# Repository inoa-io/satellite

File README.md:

# Inoa Satellite

The Inoa Satellite is a lightweight and secure gateway for your fuse box or industrial environment.

Please see our [Project Pages](https://inoa-io.github.io/satellite/) for details.

## Why?

There is a huge amount of IoT gateways out there, but none of these fulfill completely all of our design goals:

* Usage in a rough industrial environment
* Hardware driven security (HSM)
* Inexpensive hardware to be able to finance a huge fleet of devices
* Low energy consumption
* Fuse box casing (DIN rail)
* Small (2 FE / 36 mm) to allow mounting in existing fuse boxes
* Extendable design to be future proof
* Modular design to adapt hardware to use cases and keep costs low

## How?

We use [KiCad](https://www.kicad.org/) for our PCB designs, [Parts Community](https://b2b.partcommunity.com/) and [SnapEDA](https://www.snapeda.com/) for symbols, footprints, models 'n stuff...

To meet our design goals, we decided to:

* Use the ESP32
* Use the ATECC family of chips as HSM
* Choose industrial proof parts, shielding and ESD protection
* Pick a certified DIN rail casing
* Cut the design to several stacked modules

## Modules

### General

The Satellite comes with a stacked design allowing to interchange the modules on each level of the stack to fit the needs of its planned duty.

This allows quick and cheap adjustment of single devices, ensures expandability, keeps costs low and offers replacement of defect modules with spare parts.

The Satellite consists of up to 4 levels (level 1 is the bottom). Level 3 is an optional level and may be left out.

* Level 1 holds the power supply and metering / control peripheries.
* Level 2 is the main module for the micro controller
* Level 3 is the network / communication level (Ethernet, NB IoT, LoRa, ...)
* Level 4 is meant for the user panel

### Metering Modules

#### Electric Metering Module

The electric metering module is dedicated to be used for interacting with electric meters, inverters, batteries and so on. It is a base module on level 1 of the stack. Its features are:

* 5V-24V power input
* PE / Shield pin
* 2x RS485 interface (used for e.g. ModBus, ...)
* 2x pulse interface (S0, Photoelectric barrier, ...)
* 2x relay driver

#### CT Metering Module

The CT module is dedicated to be used for EMS use cases. Current transformers (split core) with voltage output may be used (e.g. SCT-013).

It is a base module on level 1 of the stack. Its features are:

* 5V-24V power input
* 3x CT
* 1x Analog in (ADC)
* 1x Digital in (e.g. S0 meters)
* 1x RS485 interface (ModBus RTU meters)

#### MBus / WMBus Metering Module

The M-Bus module is dedicated to be used for interacting with different meters via RS485 or M-Bus. The module acts as M-Bus master, but a separate power supply is needed. Because the size of this power supply depends on the amount of connected meters, we decided to give the ability to choose a fitting, external power supply.

The M-Bus module is a base module on level 1 of the stack. Its features are:

* 5V-24V power input
* 1x M-Bus interface
* 1x RS485 interface (ModBus RTU meters)
* 2x pulse interface (S0 meters)
* PE / Shield pins for bus connections

### SoC Module

The SoC module is the heart of the satellite and home of the microprocessor, flash memory and HSM (hardware security module). It is the main module on level 2 of the stack. Its features are:

* ESP32 MPU (32 Bit, Dual Core, 240 MHz)
* 8 MB RAM
* 16 MB flash
* µSD Card slot for external storage
* HSM (ATECC608)

### Ethernet Module

The Ethernet module connects the Satellite to Ethernet. It is a network module on level 3 of the stack. Its features are:

* W5500 Ethernet chip (MAC+PHY)
* ESD protection
* Shielded RJ45 plug

### NB IoT Module

_**Coming soon**_

### LoRa Module

_**Coming soon**_

### Panel Module

The panel module is the "user interface" and home of all user input output devices of the Satellite. It is the top module on level 4. Its features are:

* Power and status LED
* Reset and setup button
* 128x64 OLED display (optional)
* RS232 Debug interface
* External WiFi antenna (optional)

## Casings

We use a DIN rail mounted casing in 2 FE width. See [Datasheet](./casing/rail/apra_rail_Leiterkartengroessen_PCB_Dimensions_de_en.pdf) for details.

## Development

### Building the Project

You will need:

* Python >= 3.8
* [KiBot](https://github.com/INTI-CMNB/KiBot) (see [installation instructions](https://github.com/INTI-CMNB/KiBot#installation-on-ubuntu-or-debian))

Clone this project and run `./build.sh`. You will get a selection of the possible modules to be built. Tests will be executed and the build result is placed in the `out` folder.

### Project structure

| Folder               | Purpose |
|----------------------|---------|
| ./casing             | Construction files for the casing          |
| ./configs            | KiCad-Export configuration                 |
| ./development-board  | Design for the development board           |
| ./docs               | Documentation                              |
| ./ethernet-extension | Design for the Ethernet module             |
| ./libraries          | Electric symbols, footprints and 3D models |
| ./metering-module    | Design for the metering module             |
| ./nbiot-extension    | Design for the NB IoT module               |
| ./out                | Build output folder                        |
| ./panel-module       | Design for the panel module                |
| ./soc-module         | Design for the SoC module                  |

### Conventions

#### Markings

* Each PCB has an etched label for "TOP" and "BOT" marks
* Each PCB has an etched label for the product serial following the pattern: SR-XX-NNN (e.g. SR-SM-021)
* The product serial start with "SR" for "Satellite Rail", the next two characters are reserved for the module, the 3 digits represents the version

| Serial    | Module / Part          | Current Version |
|-----------|------------------------|-----------------|
| SR-SC-XXX | SoC Module             | v2.0            |
| SR-EM-XXX | Electric Metering      | v2.0            |
| SR-CM-XXX | Current Loop Metering  | v2.0            |
| SR-MM-XXX | MBus / WMBus Metering  | v2.0            |
| SR-ET-XXX | Ethernet Module        | v2.0            |
| SR-NB-XXX | NB IoT Module          | v2.0            |
| SR-LR-XXX | LoRa / LoRa WAN Module | v2.0            |
| SR-PN-XXX | Panel Module           | v2.0            |

#### Tracks / Vias / Grids

Despite of the low energy consumption of the MCU itself, we are planning with a maximum current of 1A to be future proof for extra extensions that have a higher energy demand (LoRa, NB IoT, ...).

We chose two different of track widths for main power and for data lines (0.25 mm / 0.5 mm) and planned a minimum temperature of 0°C. See the table below.

| Track (mm) | Track (mil) | 10°  | 20°  | 30°  | 40°  | 50°  | 60°  |
|------------|-------------|------|------|------|------|------|------|
| 0.1mm      | 4mil        | 0.4A | 0.6A | 0.8A | 0.9A | 1.0A | 1.1A |
| 0.2mm      | 8mil        | 0.7A | 1.0A | 1.2A | 1.4A | 1.6A | 1.7A |
| 0.3mm      | 12mil       | 0.9A | 1.3A | 1.6A | 1.8A | 2.0A | 2.2A |
| 0.4mm      | 16mil       | 1.1A | 1.5A | 1.9A | 2.2A | 2.4A | 2.7A |
| 0.5mm      | 20mil       | 1.3A | 1.8A | 2.2A | 2.5A | 2.8A | 3.1A |
| 0.6mm      | 24mil       | 1.4A | 2.0A | 2.4A | 2.8A | 3.1A | 3.4A |

We chose a 0.1mm grid for all PCB designs, because our casings and mechanics are also measured in millimeters.

We chose 0.8mm 0.4mm vias.

## Pin Out

| Pin ESP | Pin Satellite | Pin Name  | Standard Purpose     |
|---------|---------------|-----------|----------------------|
| 1       | East 1        | GND       | Ground               |
| 2       | West 1        | 3V3       | Power supply         |
| 3       | West 2        | EN3       | Reset                |
| 4       | West 3        | I36       | I2C Interrupt        |
| 5       | West 4        | I39       | UART 1 RX            |
| 6       | West 5        | I34       | SPI 2 MISO           |
| 7       | West 6        | I35       | UART 2 RX            |
| 8       | West 7        | IO32      | SPI 2 MOSI           |
| 9       | West 8        | IO33      | SPI 2 CLK            |
| 10      | West 9        | IO25      | UART 1 TXE           |
| 11      | West 10       | IO26      | UART 1 TX            |
| 12      | West 11       | IO27      | SPI 2 CS (Ethernet)  |
| 13      | West 12       | IO14      | Ethernet Reset       |
| 14      | West 13       | IO12      |                      |
| 15      | NC            | GND       | Ground               |
| 16      | West 14       | IO13      | Status LED           |
| 17      | NC            | NC        | Internal Flash / RAM |
| 18      | NC            | NC        | Internal Flash / RAM |
| 19      | NC            | NC        | Internal Flash / RAM |
| 20      | NC            | NC        | Internal Flash / RAM |
| 21      | NC            | NC        | Internal Flash / RAM |
| 22      | NC            | NC        | Internal Flash / RAM |
| 23      | East 13       | IO15      | UART 2 TX            |
| 24      | East 12       | IO2       | UART 2 TXE           |
| 25      | East 11       | IO0       | Setup Button         |
| 26      | East 10       | IO4       | Ethernet Interrupt   |
| 27      | NC            | NC        | Internal Flash / RAM |
| 28      | NC            | NC        | Internal Flash / RAM |
| 29      | East 9        | IO5       | SPI 1 CS (SD)        |
| 30      | East 8        | IO18      | SPI 1 CLK            |
| 31      | East 7        | IO19      | SPI 1 MISO           |
| 32      | NC            | NC        | Internal Flash / RAM |
| 33      | East 6        | IO21      | I2C SDA              |
| 34      | East 5        | URXD0     | UART 0 RX            |
| 35      | East 4        | UTXD0     | UART 0 TX            |
| 36      | East 3        | IO22      | I2C SCL              |
| 37      | East 2        | IO23      | SPI 1 MOSI           |
| 38      | East 1        | GND       | Ground               |
| NC      | East 14       | Shield    | Shield / PE          |

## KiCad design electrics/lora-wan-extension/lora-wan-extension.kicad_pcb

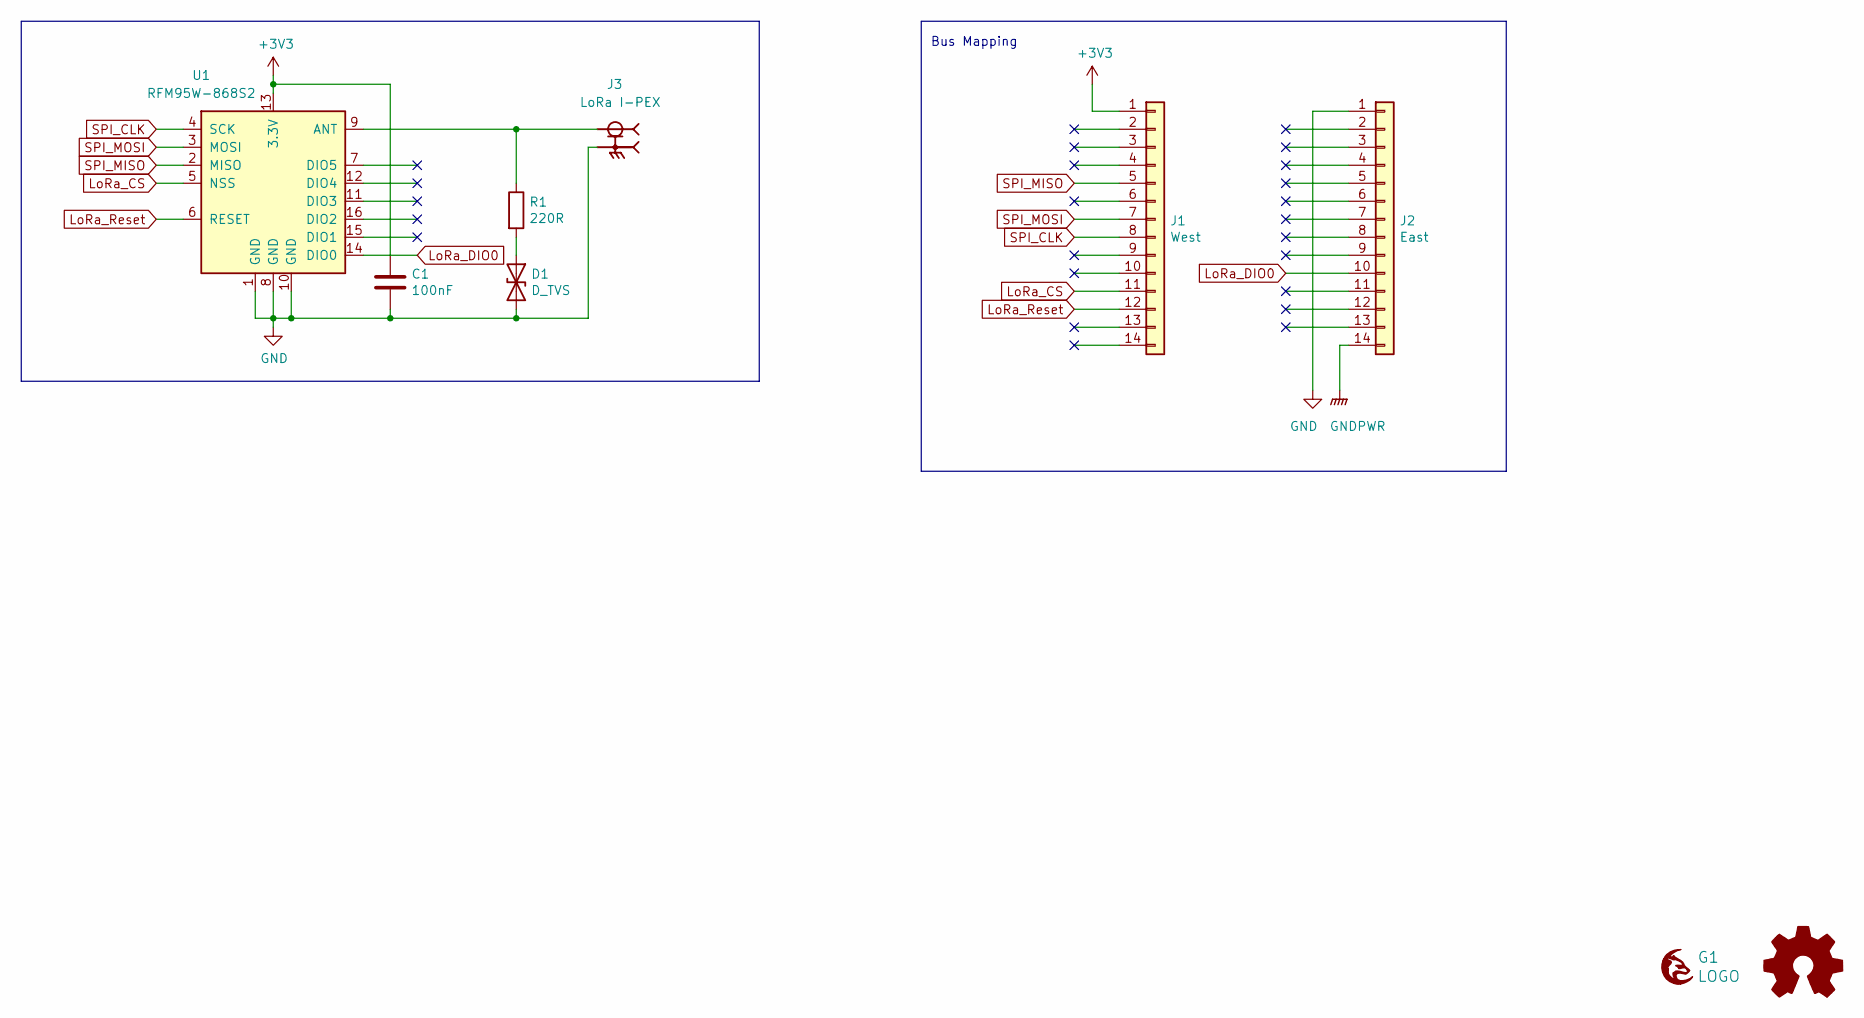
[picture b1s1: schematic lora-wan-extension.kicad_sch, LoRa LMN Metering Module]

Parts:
C1: 100nF; C_1206_3216Metric_Pad1.33x1.80mm_HandSolder; mouser# 80-C1206C104M6R
D1: D_TVS; D_0603_1608Metric_Pad1.05x0.95mm_HandSolder; mouser# 652-CG0603MLC-3.3LE
G1: LOGO; grayc-logo-negative
G2: Logo_Open_Hardware_Small; OSHW-Logo2_7.3x6mm_SilkScreen
J1: West; PinHeader_1x14_P2.54mm_Vertical; mouser# 437-8018701453001101
J2: East; PinHeader_1x14_P2.54mm_Vertical; mouser# 437-8018701453001101
J3: LoRa I-PEX; SAMTEC_RSP-122811-01; PARTREV H; mouser# 200-RSP-122811-01
R1: 220R; R_1206_3216Metric_Pad1.30x1.75mm_HandSolder; mouser# 71-RCG1206220RJNEA
U1: RFM95W-868S2; XCVR_RFM69HW-868S2; mouser# 223-RFM95W-868S2

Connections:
+3V3: C1.1, J1.1, U1.13 (3.3V)
GND: C1.2, D1.2 (A2), J2.1, J3.G1, J3.G2, U1.1 (GND), U1.8 (GND), U1.10 (GND)
GNDPWR: J2.14
LoRa_CS: J1.11, U1.5 (NSS)
LoRa_DIO0: J2.10, U1.14 (DIO0)
LoRa_Reset: J1.12, U1.6 (RESET)
unnamed: D1.1 (A1), R1.2
unnamed: J3.1, R1.1, U1.9 (ANT)
SPI_CLK: J1.8, U1.4 (SCK)
SPI_MISO: J1.5, U1.2 (MISO)
SPI_MOSI: J1.7, U1.3 (MOSI)

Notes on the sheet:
Bus Mapping

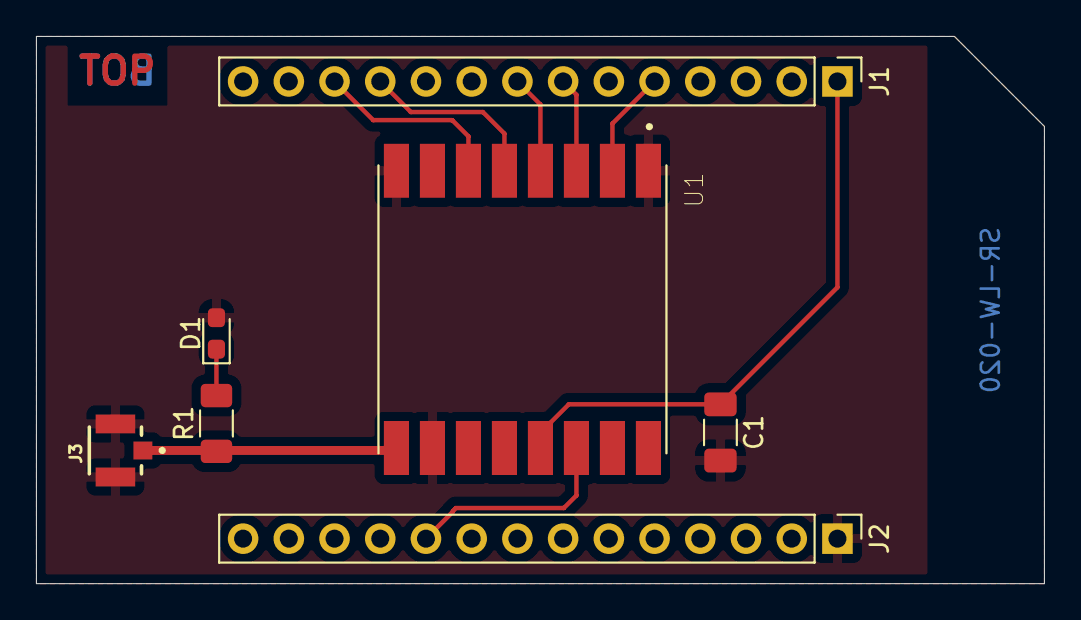
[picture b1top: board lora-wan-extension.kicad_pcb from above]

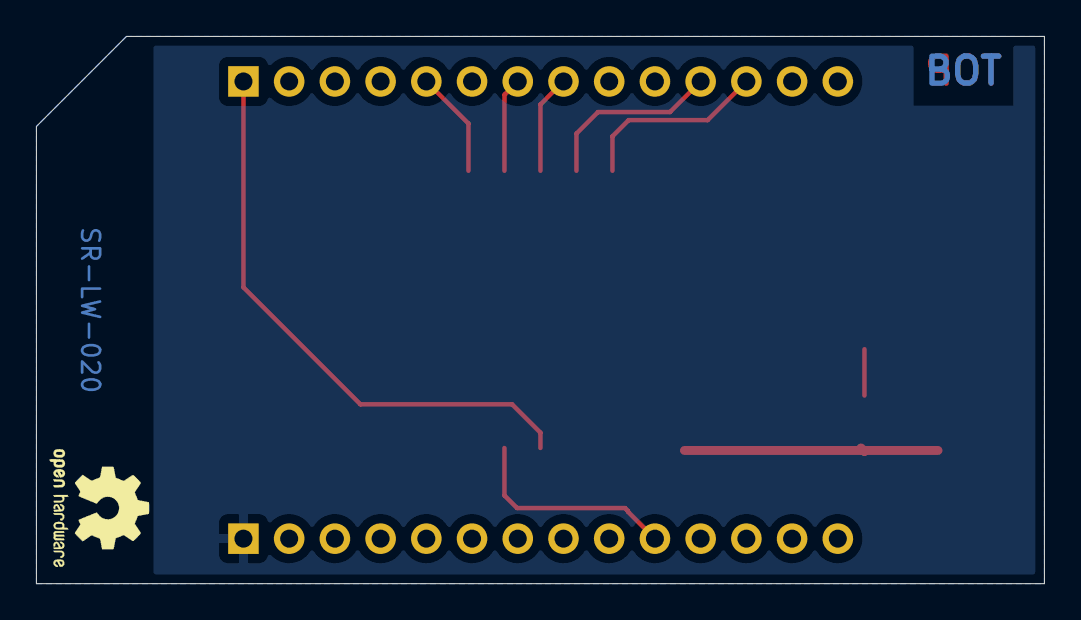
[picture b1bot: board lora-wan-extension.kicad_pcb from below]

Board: 2 copper layers, 56.0 x 30.4 mm, 9 parts (2 on the bottom side), 10 nets.

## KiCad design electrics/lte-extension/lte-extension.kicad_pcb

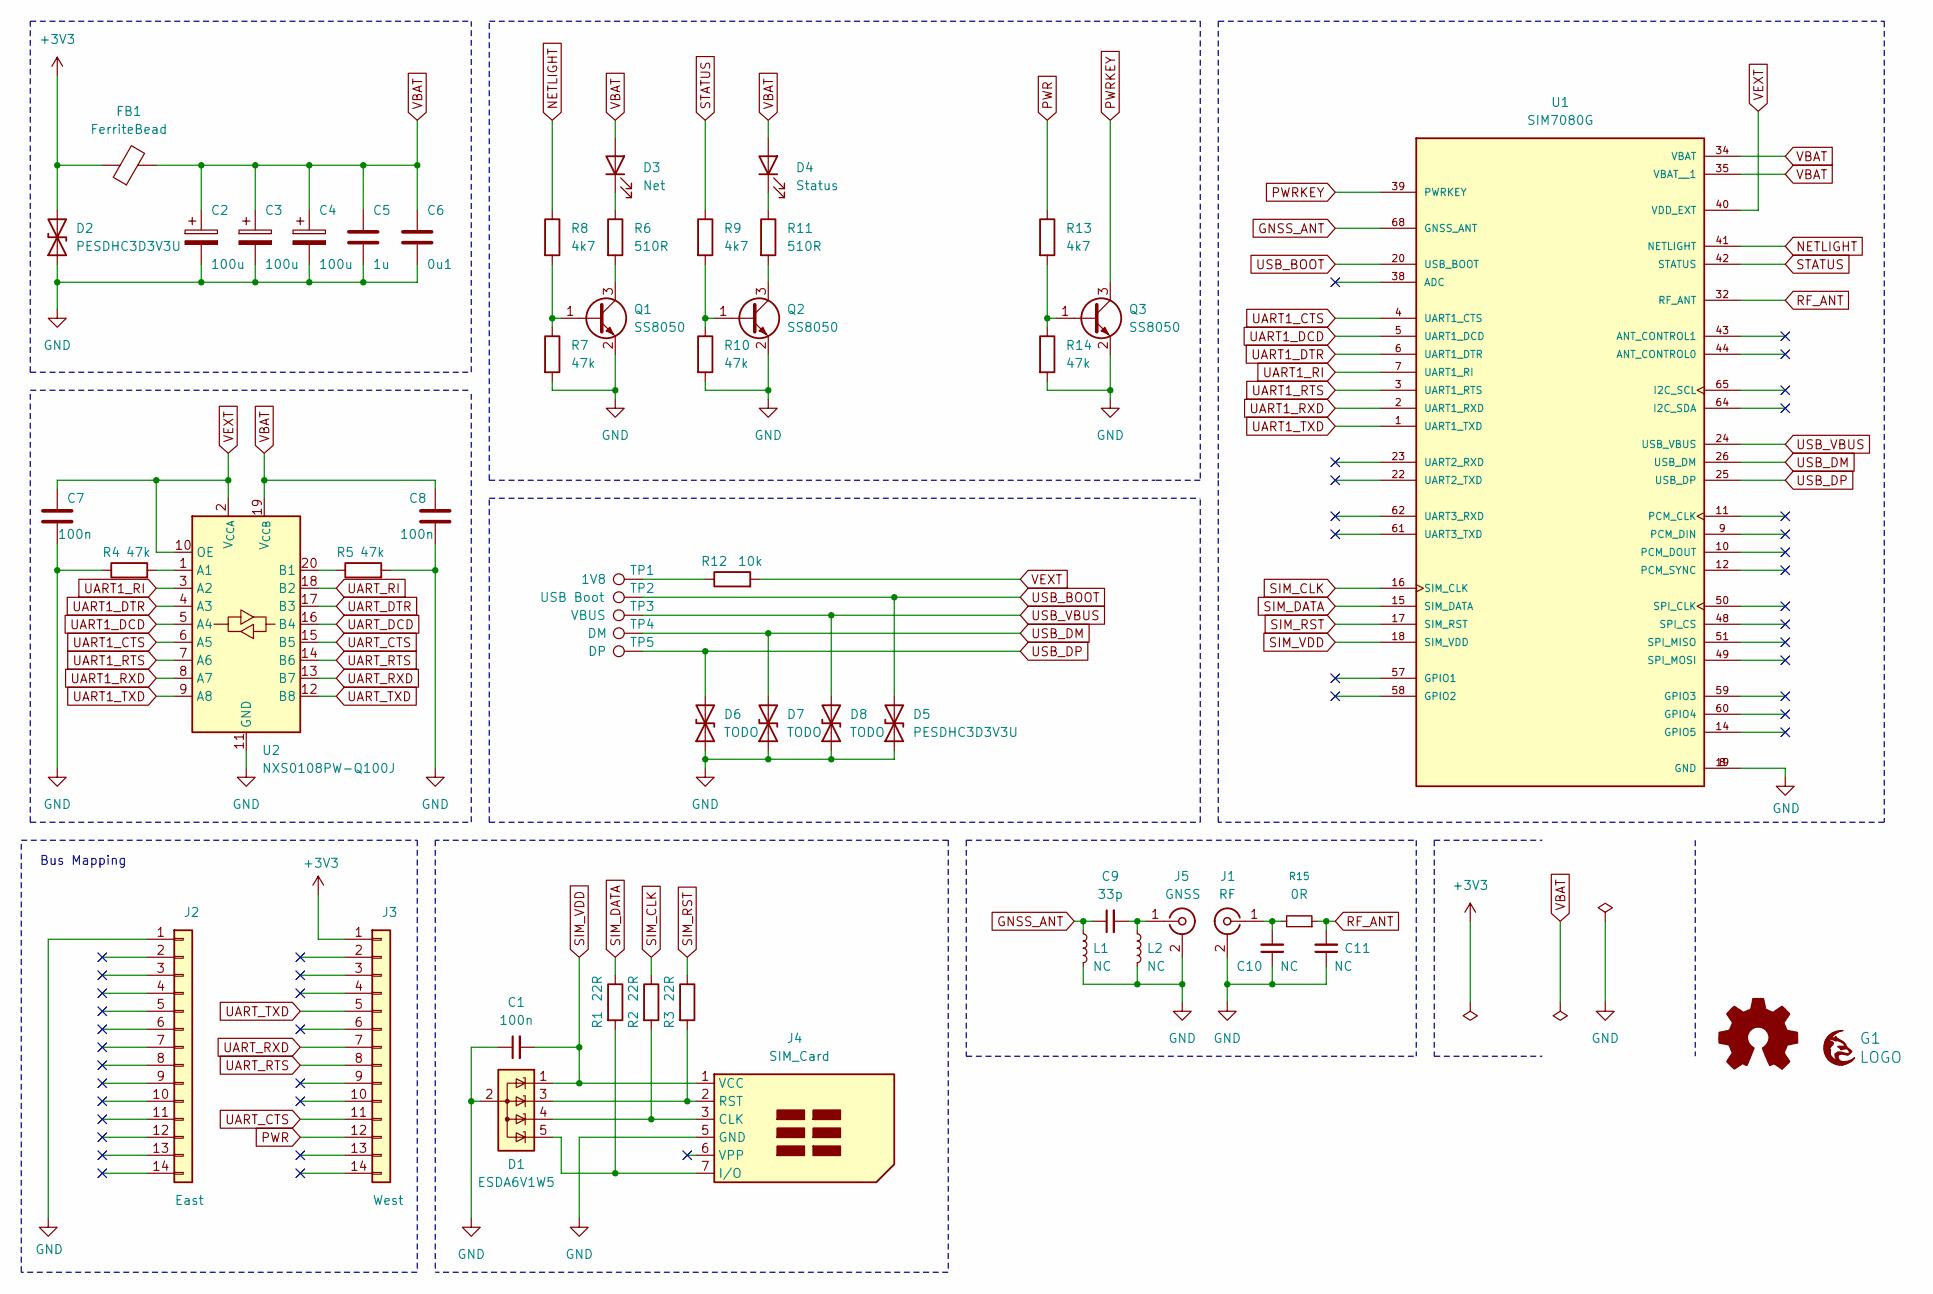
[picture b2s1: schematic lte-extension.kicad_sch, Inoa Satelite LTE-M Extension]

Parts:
C1, C7, C8: 100n; C_0603_1608Metric_Pad1.08x0.95mm_HandSolder
C2, C3, C4: 100u; CP_EIA-2012-12_Kemet-R_HandSolder
C5: 1u; C_0603_1608Metric_Pad1.08x0.95mm_HandSolder
C6: 0u1; C_0603_1608Metric_Pad1.08x0.95mm_HandSolder
C9: 33p; C_0603_1608Metric_Pad1.08x0.95mm_HandSolder
C10, C11: NC; C_0603_1608Metric_Pad1.08x0.95mm_HandSolder
D1: ESDA6V1W5; SOT65P210X110-5N
D2, D5: PESDHC3D3V3U; D_SOD-323F
D3: Net; LED_0603_1608Metric
D4: Status; LED_0603_1608Metric
D6, D7, D8: TODO; D_SOD-323F
FB1: FerriteBead; L_0805_2012Metric
G1: LOGO; grayc-logo-negative
G2: Logo_Open_Hardware_Small; OSHW-Logo2_7.3x6mm_SilkScreen
J1: RF; IPEX_20279-001E-01
J2: East; PinHeader_1x14_P2.54mm_Vertical; mouser# 437-8018701453001101
J3: West; PinHeader_1x14_P2.54mm_Vertical; mouser# 437-8018701453001101
J4: SIM_Card; nanoSIM_Hinged_CUI_NSIM-2-C
J5: GNSS; IPEX_20279-001E-01
L1, L2: NC; L_0603_1608Metric_Pad1.05x0.95mm_HandSolder
Q1, Q2, Q3: SS8050; SOT-23
R1, R2, R3: 22R; R_0603_1608Metric_Pad0.98x0.95mm_HandSolder
R4, R5, R7, R10, R14: 47k; R_0603_1608Metric_Pad0.98x0.95mm_HandSolder
R6, R11: 510R; R_0603_1608Metric_Pad0.98x0.95mm_HandSolder
R8, R9, R13: 4k7; R_0603_1608Metric_Pad0.98x0.95mm_HandSolder
R12: 10k; R_0603_1608Metric_Pad0.98x0.95mm_HandSolder
R15: 0R; R_0603_1608Metric_Pad0.98x0.95mm_HandSolder
TP1: 1V8; TestPoint_Pad_D1.0mm
TP2: USB Boot; TestPoint_Pad_D1.0mm
TP3: VBUS; TestPoint_Pad_D1.0mm
TP4: DM; TestPoint_Pad_D1.0mm
TP5: DP; TestPoint_Pad_D1.0mm
U1: SIM7080G; XCVR_SIM7080G; PARTREV 1.04
U2: NXS0108PW-Q100J; TSSOP-20_4.4x6.5mm_P0.65mm

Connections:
+1V8: C7.1, R12.2, U1.40 (VDD_EXT), U2.2 (V_{CCA}), U2.10 (OE)
+3V3: D2.2 (A2), FB1.1, J3.1
GND: C1.1, C2.2, C3.2, C4.2, C5.2, C6.2, C7.2, C8.2, C10.1, C11.1, D1.2 (A), D2.1 (A1), D5.1 (A1), D6.1 (A1), D7.1 (A1), D8.1 (A1), J1.2 (Ext), J2.1, J4.5 (GND), J5.2 (Ext), L1.2, L2.2, Q1.2 (E), Q2.2 (E), Q3.2 (E), R4.1, R5.2, R7.2, R10.2, R14.2, U1.8 (GND), U1.13 (GND), U1.19 (GND), U1.21 (GND), U1.27 (GND), U1.30 (GND), U1.31 (GND), U1.33 (GND), U1.36 (GND), U1.37 (GND), U1.45 (GND), U1.63 (GND), U1.66 (GND), U1.67 (GND), U1.69 (GND), U1.70 (GND), U1.71 (GND), U1.72 (GND), U1.73 (GND), U1.74 (GND), U1.75 (GND), U1.76 (GND), U1.77 (GND), U2.11 (GND), U2.21 (GND)
GNDPWR: J2.14
GNSS_ANT: C9.1, L1.1, U1.68 (GNSS_ANT)
NETLIGHT: R8.1, U1.41 (NETLIGHT)
unnamed: D3.1 (K), R6.1
unnamed: D4.1 (K), R11.1
unnamed: C10.2, J1.1 (In), R15.2
unnamed: D1.4 (K), J4.3 (CLK), R2.2
unnamed: D1.5 (K), J4.7 (I/O), R1.2
unnamed: D1.3 (K), J4.2 (RST), R3.2
unnamed: C9.2, J5.1 (In), L2.1
unnamed: Q1.1 (B), R7.1, R8.2
unnamed: Q1.3 (C), R6.2
unnamed: Q2.1 (B), R9.2, R10.1
unnamed: Q2.3 (C), R11.2
unnamed: Q3.1 (B), R13.2, R14.1
unnamed: R12.1, TP1.1
unnamed: R4.2, U2.1 (A1)
unnamed: R5.1, U2.20 (B1)
PWR: J3.12, R13.1
PWRKEY: Q3.3 (C), U1.39 (PWRKEY)
RF_ANT: C11.2, R15.1, U1.32 (RF_ANT)
SIM_CLK: R2.1, U1.16 (SIM_CLK)
SIM_DATA: R1.1, U1.15 (SIM_DATA)
SIM_RST: R3.1, U1.17 (SIM_RST)
SIM_VDD: C1.2, D1.1 (K), J4.1 (VCC), U1.18 (SIM_VDD)
STATUS: R9.1, U1.42 (STATUS)
UART1_CTS: U1.4 (UART1_CTS), U2.6 (A5)
UART1_DCD: U1.5 (UART1_DCD), U2.5 (A4)
UART1_DTR: U1.6 (UART1_DTR), U2.4 (A3)
UART1_RI: U1.7 (UART1_RI), U2.3 (A2)
UART1_RTS: U1.3 (UART1_RTS), U2.7 (A6)
UART1_RXD: U1.2 (UART1_RXD), U2.8 (A7)
UART1_TXD: U1.1 (UART1_TXD), U2.9 (A8)
UART_CTS: J3.11, U2.15 (B5)
UART_DCD: U2.16 (B4)
UART_DTR: U2.17 (B3)
UART_RI: U2.18 (B2)
UART_RTS: J3.8, U2.14 (B6)
UART_RXD: J3.7, U2.13 (B7)
UART_TXD: J3.5, U2.12 (B8)
USB_BOOT: D5.2 (A2), TP2.1, U1.20 (USB_BOOT)
USB_DM: D7.2 (A2), TP4.1, U1.26 (USB_DM)
USB_DP: D6.2 (A2), TP5.1, U1.25 (USB_DP)
USB_VBUS: D8.2 (A2), TP3.1, U1.24 (USB_VBUS)
VBAT: C2.1, C3.1, C4.1, C5.1, C6.1, C8.1, D3.2 (A), D4.2 (A), FB1.2, U1.34 (VBAT), U1.35 (VBAT__1), U2.19 (V_{CCB})

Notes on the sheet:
Bus Mapping

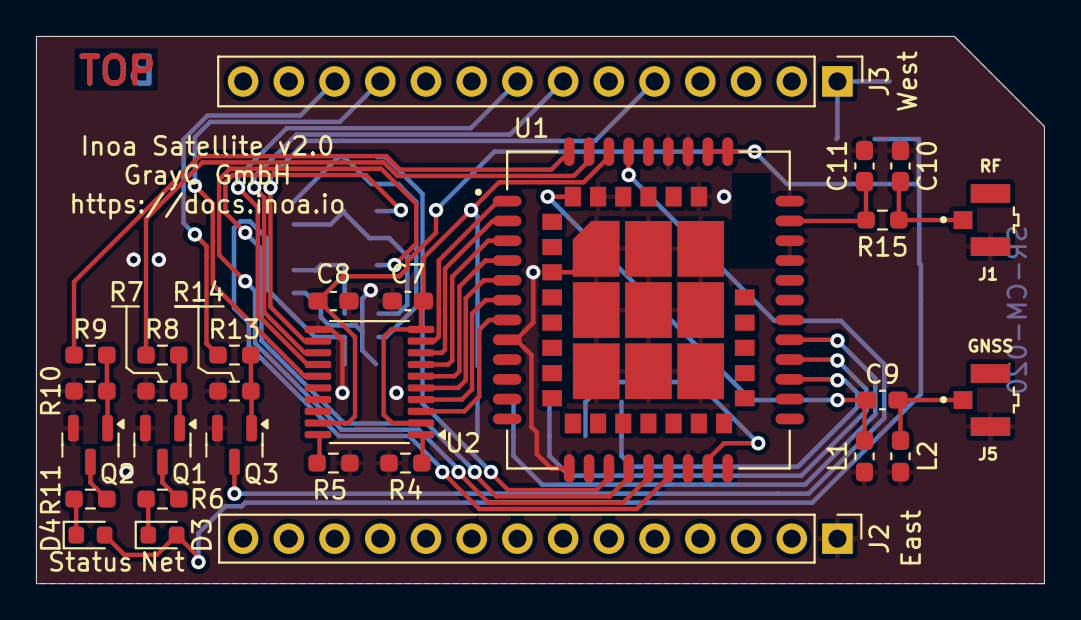
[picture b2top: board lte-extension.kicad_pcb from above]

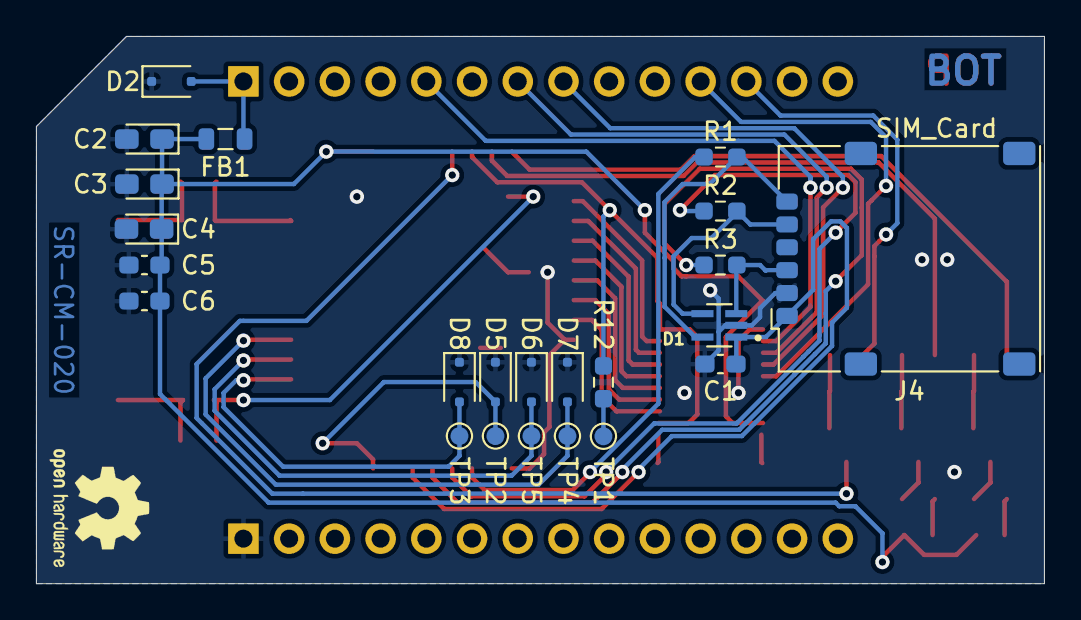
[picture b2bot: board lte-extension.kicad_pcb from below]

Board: 2 copper layers, 56.0 x 30.4 mm, 54 parts (25 on the bottom side), 44 nets.

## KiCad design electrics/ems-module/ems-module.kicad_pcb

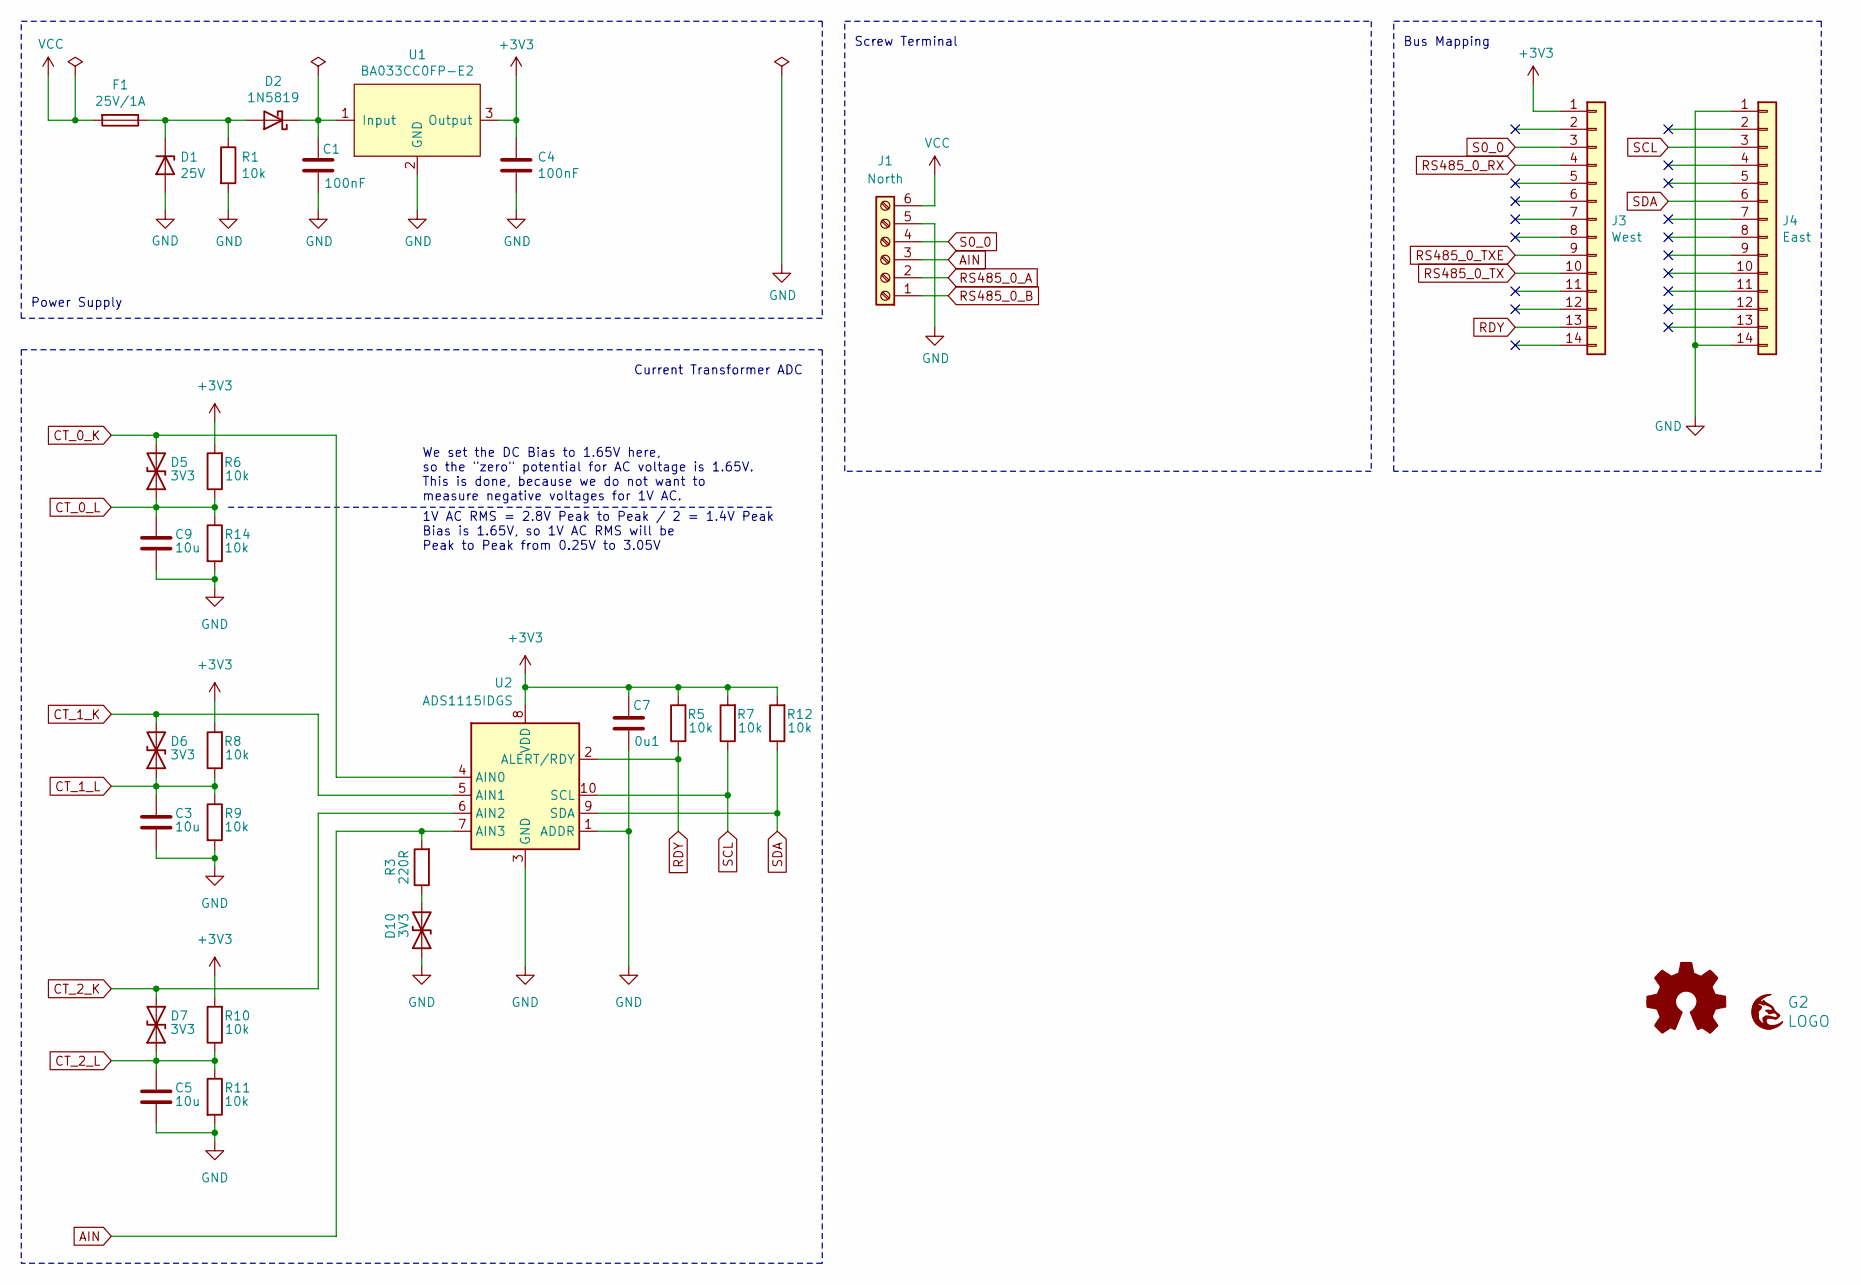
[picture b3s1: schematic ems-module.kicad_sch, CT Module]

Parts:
C1, C4: 100nF; C_1206_3216Metric_Pad1.33x1.80mm_HandSolder; mouser# 80-C1206C104M5R
C3, C5, C9: 10u; C_1206_3216Metric_Pad1.33x1.80mm_HandSolder; mouser# 80-C1206C106M9R
C7: 0u1; C_1206_3216Metric_Pad1.33x1.80mm_HandSolder; mouser# 80-C1206C104M5R
D1: 25V; D_SOD-123; mouser# 78-MMSZ5253C-E3-08
D2: 1N5819; D_SOD-323_HandSoldering; mouser# 771-PMEG4010CEAX
D5, D6, D7, D10: 3V3; D_0603_1608Metric_Pad1.05x0.95mm_HandSolder; mouser# 652-CG0603MLC-3.3LE
F1: 25V/1A; Fuse_1206_3216Metric_Pad1.42x1.75mm_HandSolder; mouser# 504-TR/3216FF1-R
G1: Logo_Open_Hardware_Small; OSHW-Logo2_7.3x6mm_SilkScreen
G2: LOGO; grayc-logo-negative
J1: North; PHOENIX_1935200; mouser# 651-1935200
J3: West; PinHeader_1x14_P2.54mm_Vertical; mouser# 855-M20-9991446
J4: East; PinHeader_1x14_P2.54mm_Vertical; mouser# 855-M20-9991446
R1, R5, R6, R7, R8, R9, R10, R11, R12, R14: 10k; R_1206_3216Metric_Pad1.30x1.75mm_HandSolder; mouser# 652-CR1206JW-103ELF
R3: 220R; R_1206_3216Metric_Pad1.30x1.75mm_HandSolder; mouser# 652-CR0603FX-2200ELF
U1: BA033CC0FP-E2; TO-252-3_TabPin2; mouser# 755-BA033CC0FP-E2
U2: ADS1115IDGS; VSSOP-10_3x3mm_P0.5mm

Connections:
+3V3: C4.1, C7.2, J3.1, R5.2, R6.2, R7.2, R8.2, R10.2, R12.2, U1.3 (Output), U2.8 (VDD)
AIN: J1.3, R3.2, U2.7 (AIN3)
CT_0_K: D5.2 (A2), U2.4 (AIN0)
CT_0_L: C9.1, D5.1 (A1), R6.1, R14.1
CT_1_K: D6.2 (A2), U2.5 (AIN1)
CT_1_L: C3.1, D6.1 (A1), R8.1, R9.1
CT_2_K: D7.2 (A2), U2.6 (AIN2)
CT_2_L: C5.1, D7.1 (A1), R10.1, R11.1
GND: C1.2, C3.2, C4.2, C5.2, C7.1, C9.2, D1.2 (A), D10.1 (A1), J1.5, J4.1, J4.14, R1.2, R9.2, R11.2, R14.2, U1.2 (GND), U2.1 (ADDR), U2.3 (GND)
unnamed: D1.1 (K), D2.2 (A), F1.1, R1.1
unnamed: C1.1, D2.1 (K), U1.1 (Input)
unnamed: D10.2 (A2), R3.1
RDY: J3.13, R5.1, U2.2 (ALERT/RDY)
RS485_0_A: J1.2
RS485_0_B: J1.1
RS485_0_RX: J3.4
RS485_0_TX: J3.10
RS485_0_TXE: J3.9
S0_0: J1.4, J3.3
SCL: J4.3, R7.1, U2.10 (SCL)
SDA: J4.6, R12.1, U2.9 (SDA)
VCC: F1.2, J1.6

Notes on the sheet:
Bus Mapping
1V AC RMS = 2.8V Peak to Peak / 2 = 1.4V Peak Bias is 1.65V, so 1V AC RMS will be Peak to Peak from 0.25V to 3.05V
We set the DC Bias to 1.65V here, so the "zero" potential for AC voltage is 1.65V. This is done, because we do not want to measure negative voltages for 1V AC.
Current Transformer ADC
Power Supply
Screw Terminal

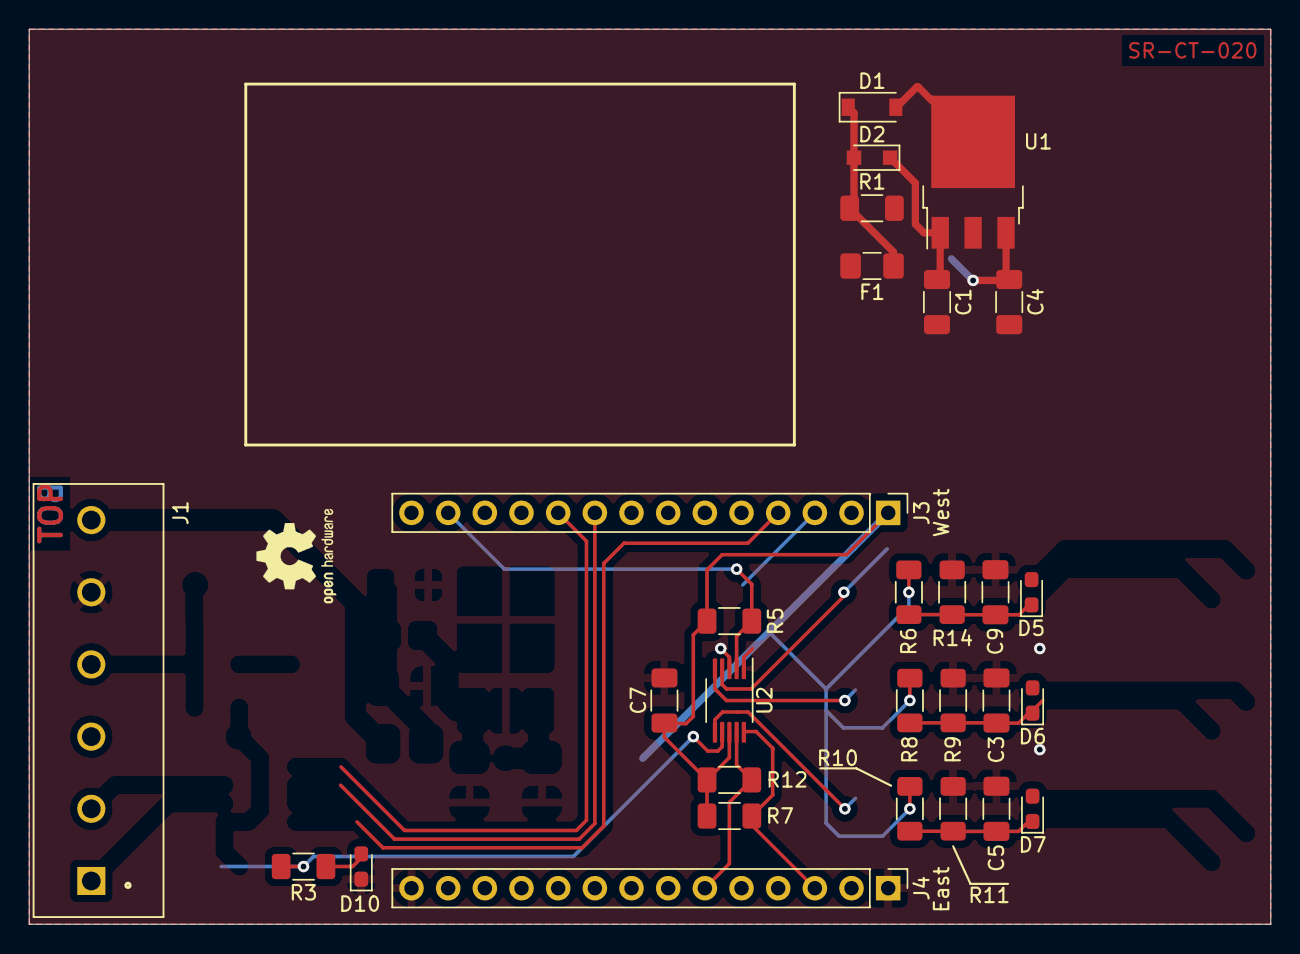
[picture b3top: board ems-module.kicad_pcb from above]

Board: 2 copper layers, 86.0 x 62.0 mm, 31 parts (1 on the bottom side), 17 nets.

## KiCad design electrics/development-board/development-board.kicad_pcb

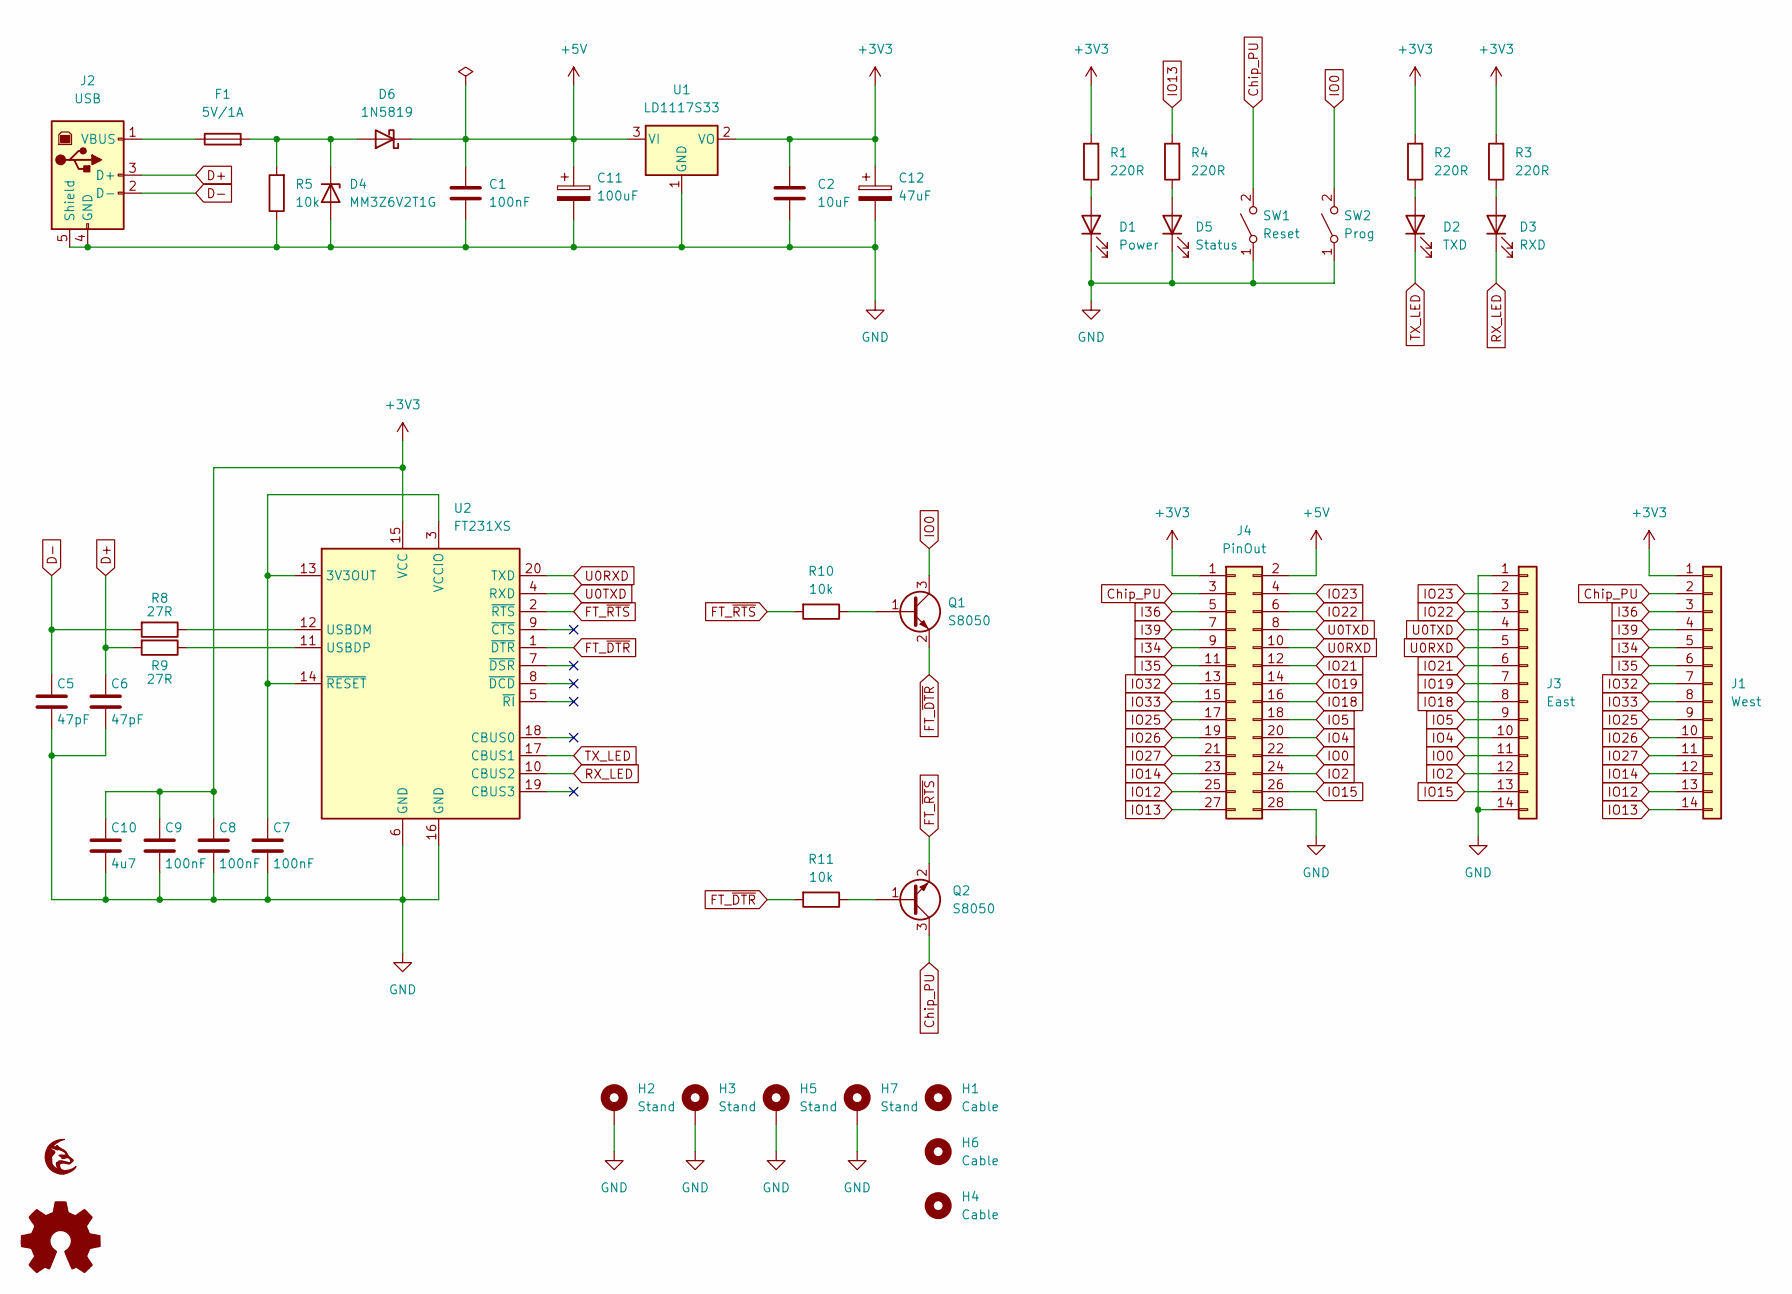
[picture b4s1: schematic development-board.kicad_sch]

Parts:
C1, C7, C8, C9: 100nF; C_1206_3216Metric_Pad1.33x1.80mm_HandSolder
C2: 10uF; C_1206_3216Metric_Pad1.33x1.80mm_HandSolder
C5, C6: 47pF; C_1206_3216Metric_Pad1.33x1.80mm_HandSolder
C10: 4u7; C_1206_3216Metric_Pad1.33x1.80mm_HandSolder
C11: 100uF; CP_Elec_6.3x5.4
C12: 47uF; CP_Elec_6.3x5.4
D1: Power; LED_1206_3216Metric_Pad1.42x1.75mm_HandSolder
D2: TXD; LED_1206_3216Metric_Pad1.42x1.75mm_HandSolder
D3: RXD; LED_1206_3216Metric_Pad1.42x1.75mm_HandSolder
D4: MM3Z6V2T1G; D_SOD-123F
D5: Status; LED_1206_3216Metric_Pad1.42x1.75mm_HandSolder
D6: 1N5819; D_SOD-323_HandSoldering
F1: 5V/1A; Fuse_1206_3216Metric_Pad1.42x1.75mm_HandSolder
G1: LOGO; grayc-logo-negative
H1, H4, H6: Cable; MountingHole_5.5mm
H2, H3, H5, H7: Stand; MountingHole_3.2mm_M3_DIN965_Pad
J1: West; PinHeader_1x14_P2.54mm_Vertical
J2: USB; USB_B_OST_USB-B1HSxx_Horizontal
J3: East; PinHeader_1x14_P2.54mm_Vertical
J4: PinOut; PinHeader_2x14_P2.54mm_Vertical
LOGO1: Logo_Open_Hardware_Small; OSHW-Logo2_7.3x6mm_SilkScreen
Q1, Q2: S8050; SOT-23-3
R1, R2, R3, R4: 220R; R_1206_3216Metric_Pad1.30x1.75mm_HandSolder
R5, R10, R11: 10k; R_1206_3216Metric_Pad1.30x1.75mm_HandSolder
R8, R9: 27R; R_1206_3216Metric_Pad1.30x1.75mm_HandSolder
SW1: Reset; SW_SPST_PTS645
SW2: Prog; SW_SPST_PTS645
U1: LD1117S33; SOT-223-3_TabPin2
U2: FT231XS; SSOP-20_3.9x8.7mm_P0.635mm

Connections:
+3V3: C2.1, C8.1, C9.1, C10.1, C12.1, J1.1, J4.1, R1.2, R2.2, R3.2, U1.2 (VO), U2.15 (VCC)
+5V: C1.1, C11.1, D6.1 (K), J4.2, U1.3 (VI)
Chip_PU: J1.2, J4.3, Q2.3 (C), SW1.2 (B)
D+: C6.1, J2.3 (D+), R9.2
D-: C5.1, J2.2 (D-), R8.2
FT_~DTR: Q1.2 (E), R11.2, U2.1 (~DTR)
FT_~RTS: Q2.2 (E), R10.2, U2.2 (~RTS)
GND: C1.2, C2.2, C5.2, C6.2, C7.2, C8.2, C9.2, C10.2, C11.2, C12.2, D1.1 (K), D4.2 (A), D5.1 (K), H2.1, H3.1, H5.1, H7.1, J2.4 (GND), J2.5 (Shield), J3.1, J3.14, J4.28, R5.1, SW1.1 (A), SW2.1 (A), U1.1 (GND), U2.6 (GND), U2.16 (GND)
I34: J1.5, J4.9
I35: J1.6, J4.11
I36: J1.3, J4.5
I39: J1.4, J4.7
IO0: J3.11, J4.22, Q1.3 (C), SW2.2 (B)
IO2: J3.12, J4.24
IO4: J3.10, J4.20
IO5: J3.9, J4.18
IO12: J1.13, J4.25
IO13: J1.14, J4.27, R4.2
IO14: J1.12, J4.23
IO15: J3.13, J4.26
IO18: J3.8, J4.16
IO19: J3.7, J4.14
IO21: J3.6, J4.12
IO22: J3.3, J4.6
IO23: J3.2, J4.4
IO25: J1.9, J4.17
IO26: J1.10, J4.19
IO27: J1.11, J4.21
IO32: J1.7, J4.13
IO33: J1.8, J4.15
unnamed: C7.1, U2.3 (VCCIO), U2.13 (3V3OUT), U2.14 (~RESET)
unnamed: D1.2 (A), R1.1
unnamed: D2.2 (A), R2.1
unnamed: D3.2 (A), R3.1
unnamed: D4.1 (K), D6.2 (A), F1.2, R5.2
unnamed: D5.2 (A), R4.1
unnamed: F1.1, J2.1 (VBUS)
unnamed: Q1.1 (B), R10.1
unnamed: Q2.1 (B), R11.1
unnamed: R8.1, U2.12 (USBDM)
unnamed: R9.1, U2.11 (USBDP)
RX_LED: D3.1 (K), U2.10 (CBUS2)
TX_LED: D2.1 (K), U2.17 (CBUS1)
U0RXD: J3.5, J4.10, U2.20 (TXD)
U0TXD: J3.4, J4.8, U2.4 (RXD)
